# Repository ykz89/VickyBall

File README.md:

# VickyBall

Based on [KeyBall](https://github.com/Yowkees/keyball) and [roBa](https://github.com/kumamuk-git/roBa).

This project is forked from [roBa](https://github.com/kumamuk-git/roBa) with the main goal to convert the trackball sensor to use [VIK](https://github.com/sadekbaroudi/vik). The name VickyBall is a combination of [VIK](https://github.com/sadekbaroudi/vik) and [KeyBall](https://github.com/Yowkees/keyball).

Full list of changes:
- Sacrifice keys to make space for changes
- Add VIK connectors to trackball module and keyboard
- Change switch footprint to support MX, Choc and GLP switches
- Change microcontroller footprint from Xiao nrf52840 to Xiao nrf52840 Plus

## Build Guide

Todo

## Firmware

Todo

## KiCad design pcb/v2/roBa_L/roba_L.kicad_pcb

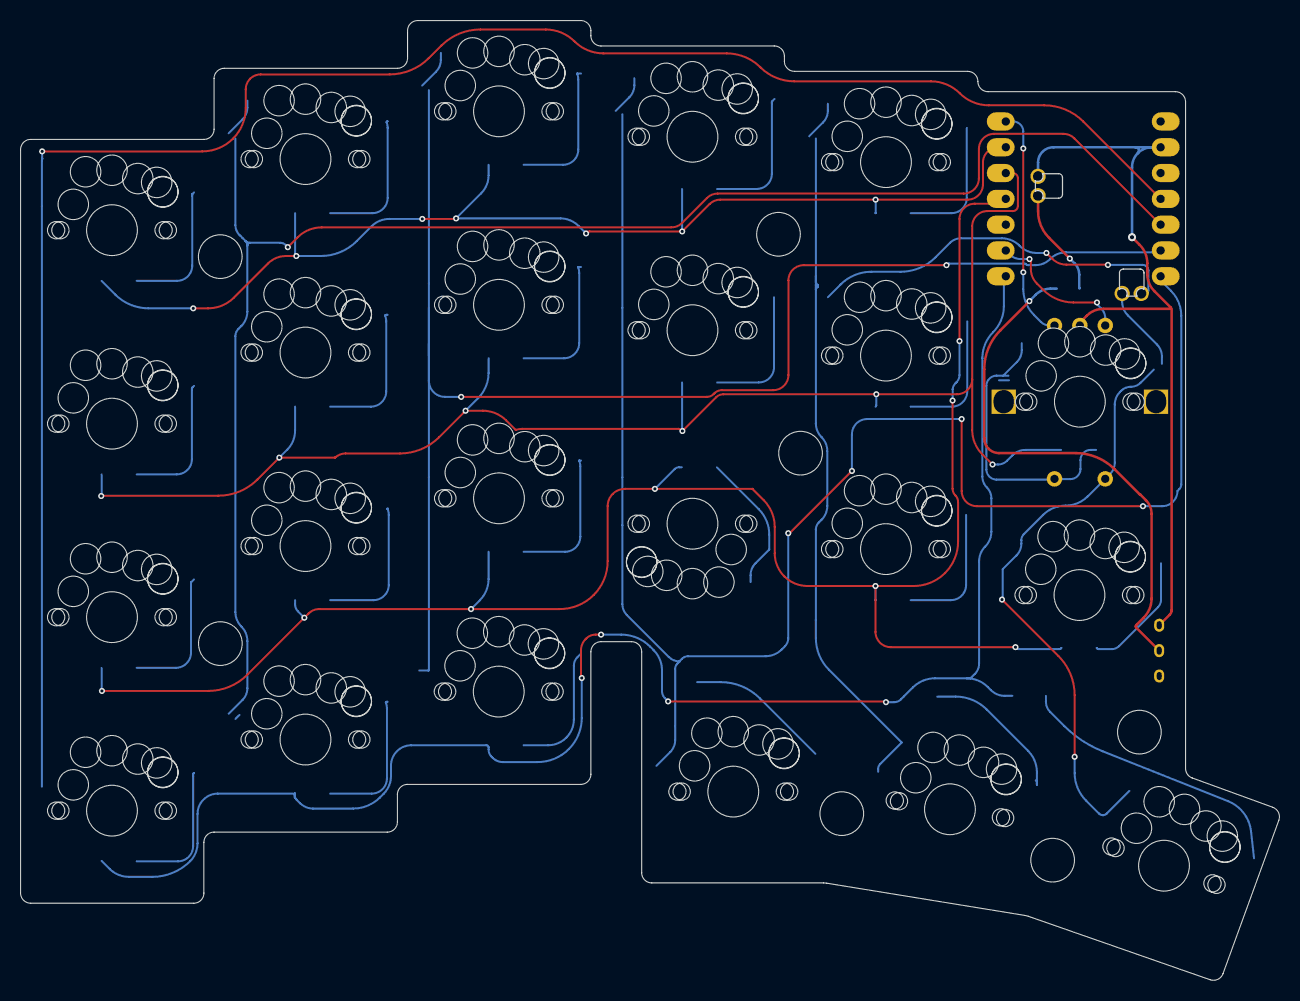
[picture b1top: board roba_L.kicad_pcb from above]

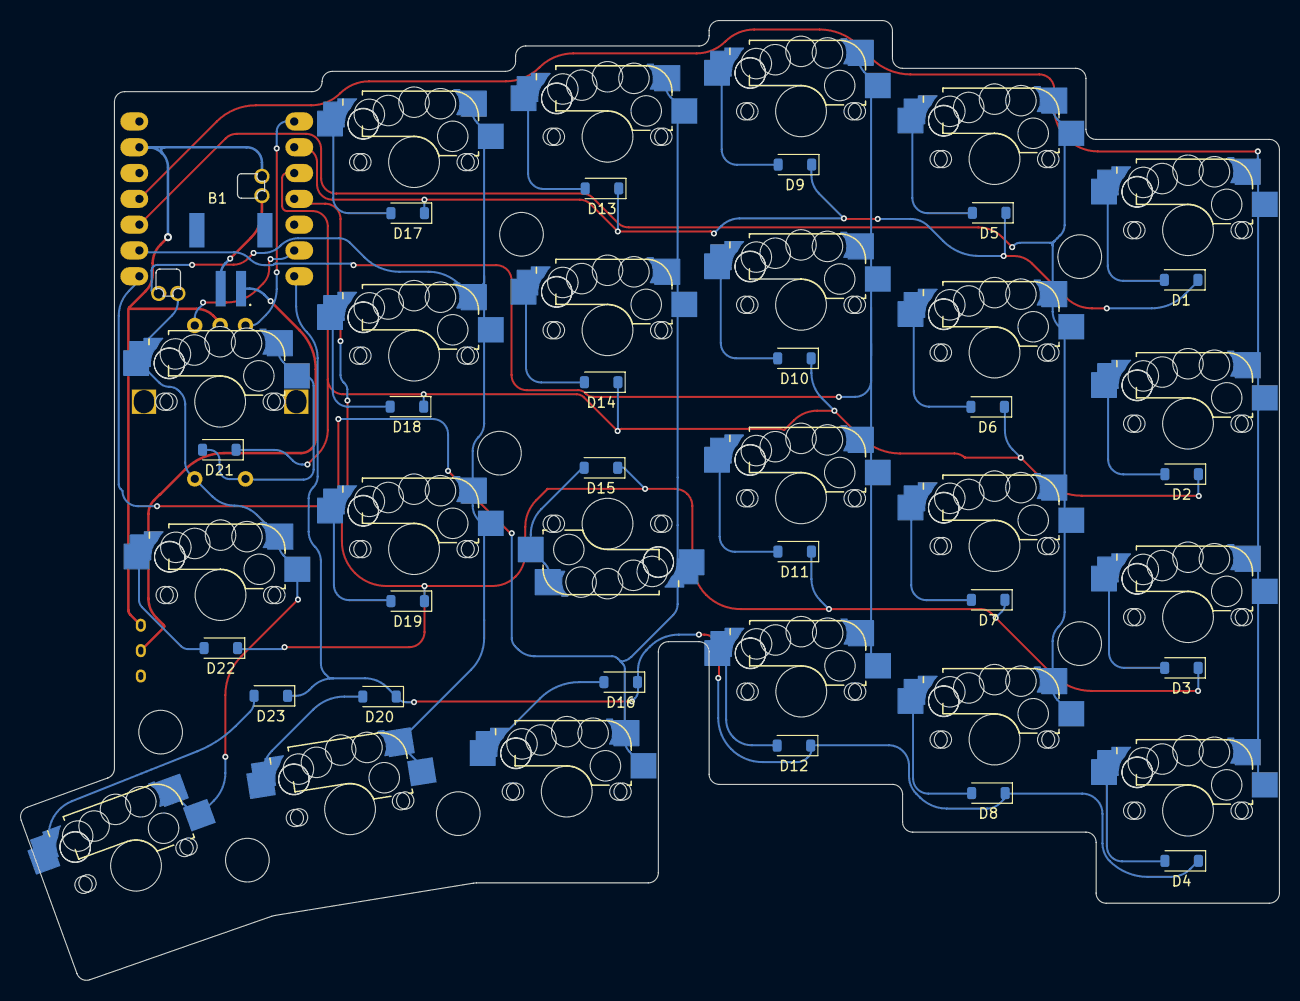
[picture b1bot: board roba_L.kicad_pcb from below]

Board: 2 copper layers, 123.9 x 94.5 mm, 56 parts (25 on the bottom side), 38 nets.

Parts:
B1: BATT; JST_S2B-PH-SM4-TB
D1, D2, D3, D4, D5, D6, D7, D8, D9, D10, D11, D12, D13, D14, D15, D16, D17, D18, D19, D20, D21, D22, D23: D; D_SOD-123
J1, J2, J3, J4, J5, J6, J7: Conn_01x01-Connector_Generic; MountingHole_4.3mm_M4
SW1, SW2, SW3, SW4, SW5, SW6, SW7, SW8, SW9, SW10, SW11, SW12, SW13, SW14, SW15, SW16, SW17, SW18, SW19, SW20, SW22, SW23: SW_PUSH; gateron-ks27-choc-v1-mx-hotswap-curved-pads
SW21: RotaryEncoder_Switch; gateron-ks27-choc-v1-mx-hotswap-ec12
SW24: SW_SPDT; TGSW_MSK-12D19
U1: XIAO_nRF52840_wBAT_wNFC_1

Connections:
Bat: B1.1 (+), U1.20 (BATT+)
Col0: SW1.2, SW2.2, SW3.2, SW4.2, U1.11 (P1.15_D10_MOSI)
Col1: SW5.2, SW6.2, SW7.2, SW8.2, U1.10 (P1.14_D9_MISO)
Col2: SW9.2, SW10.2, SW11.2, SW12.2, U1.9 (P1.13_D8_SCK)
Col3: SW13.2, SW14.2, SW15.1, SW16.2, U1.8 (P1.12_D7_RX)
Col4: SW17.2, SW18.2, SW19.2, SW20.2, U1.16 (NFC2_0.10)
Col5: SW21.1, SW21.2, SW22.2, SW23.2, U1.15 (NFC1_0.09)
GND: SW21.C, SW24.3 (C), U1.13 (GND), U1.21 (BATT-)
unnamed: B1.2 (-), SW24.2 (B)
unnamed: D1.2 (A), SW1.1
unnamed: D2.2 (A), SW2.1
unnamed: D3.2 (A), SW3.1
unnamed: D4.2 (A), SW4.1
unnamed: D5.2 (A), SW5.1
unnamed: D6.2 (A), SW6.1
unnamed: D7.2 (A), SW7.1
unnamed: D8.2 (A), SW8.1
unnamed: D9.2 (A), SW9.1
unnamed: D10.2 (A), SW10.1
unnamed: D11.2 (A), SW11.1
unnamed: D12.2 (A), SW12.1
unnamed: D13.2 (A), SW13.1
unnamed: D14.2 (A), SW14.1
unnamed: D15.2 (A), SW15.2
unnamed: D16.2 (A), SW16.1
unnamed: D17.2 (A), SW17.1
unnamed: D18.2 (A), SW18.1
unnamed: D19.2 (A), SW19.1
unnamed: D20.2 (A), SW20.1
unnamed: D21.2 (A), SW21.1, SW21.2
unnamed: D22.2 (A), SW22.1
unnamed: D23.2 (A), SW23.1
RE_A1: SW21.A, U1.6 (P0.05_A5_D5_SCL)
RE_B: SW21.B, U1.1 (P0.02_A0_D0)
Row0: D1.1 (K), D5.1 (K), D9.1 (K), D13.1 (K), D17.1 (K), U1.2 (P0.03_A1_D1)
Row1: D2.1 (K), D6.1 (K), D10.1 (K), D14.1 (K), D18.1 (K), D21.1 (K), U1.3 (P0.28_A2_D2)
Row2: D3.1 (K), D7.1 (K), D11.1 (K), D15.1 (K), D19.1 (K), D22.1 (K), U1.4 (P0.29_A3_D3)
Row3: D4.1 (K), D8.1 (K), D12.1 (K), D16.1 (K), D20.1 (K), D23.1 (K), U1.7 (P1.11_D6_TX)

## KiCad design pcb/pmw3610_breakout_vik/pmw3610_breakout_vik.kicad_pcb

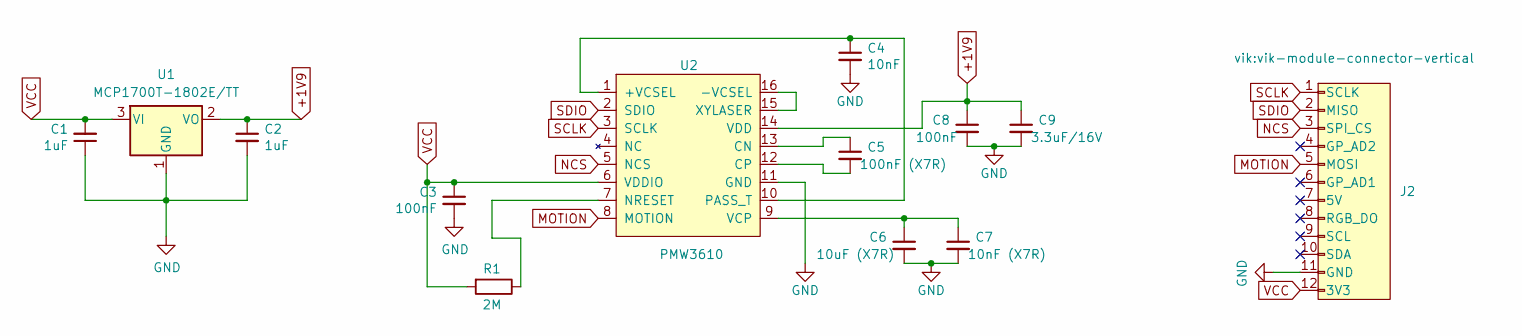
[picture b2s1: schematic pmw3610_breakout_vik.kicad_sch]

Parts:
C1, C2: 1uF; C_0603_1608Metric
C3, C8: 100nF; C_0603_1608Metric
C4: 10nF; C_0603_1608Metric
C5: 100nF (X7R); C_0603_1608Metric
C6: 10uF (X7R); C_0603_1608Metric
C7: 10nF (X7R); C_0603_1608Metric
C9: 3.3uF/16V; C_0603_1608Metric
J2: vik-module-connector; vik-module-connector-vertical
R1: 2M; R_0603_1608Metric
U1: MCP1700T-1802E/TT; SOT-23
U2: PMW3610; PMW3610DM-SUDU 16Pin

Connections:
+1V9: C2.1, C8.1, C9.1, U1.2 (VO), U2.14 (VDD)
GND: C1.1, C2.2, C3.2, C4.2, C6.2, C7.2, C8.2, C9.2, J2.11 (GND), U1.1 (GND), U2.11 (GND)
MOTION: J2.5 (MOSI), U2.8 (MOTION)
NCS: J2.3 (SPI_CS), U2.5 (NCS)
unnamed: C4.1, U2.1 (+VCSEL), U2.10 (PASS_T)
unnamed: U2.15 (XYLASER), U2.16 (-VCSEL)
unnamed: C5.1, U2.13 (CN)
unnamed: C5.2, U2.12 (CP)
unnamed: R1.1, U2.7 (NRESET)
unnamed: C6.1, C7.1, U2.9 (VCP)
SCLK: J2.1 (SCLK), U2.3 (SCLK)
SDIO: J2.2 (MISO), U2.2 (SDIO)
VCC: C1.2, C3.1, J2.12 (3V3), R1.2, U1.3 (VI), U2.6 (VDDIO)

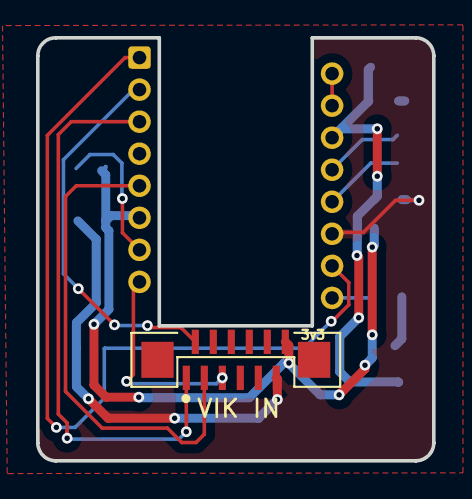
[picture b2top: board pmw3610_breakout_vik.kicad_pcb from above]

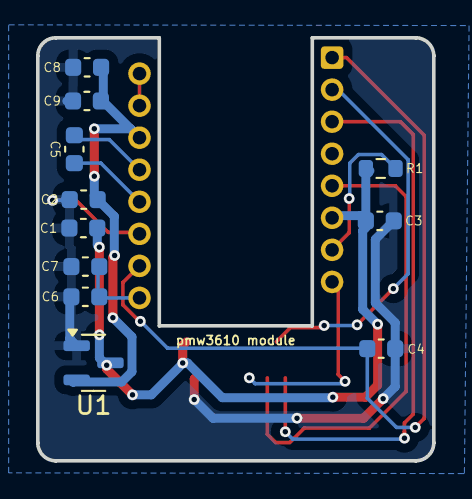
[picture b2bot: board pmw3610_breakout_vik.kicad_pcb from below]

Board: 2 copper layers, 22.0 x 23.5 mm, 13 parts (11 on the bottom side), 13 nets.

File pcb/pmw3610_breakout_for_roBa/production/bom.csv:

Designator,Footprint,Quantity,Value,LCSC Part #
"C1, C2",0603,2,1uF,C15849
"C3, C8",0603,2,100nF,C14663
C4,0603,1,10nF,C57112
C5,0603,1,100nF (X7R),C14663
C6,0603,1,10uF (X7R),C2959727
C7,0603,1,10nF (X7R),C57112
C9,0603,1,3.3uF/16V,C51412
J2,vik-module-connector-vertical,1,vik-module-connector,
R1,0603,1,2M,C22976
U1,SOT-23,1,MCP1700T-1802E/TT,
U2,PMW3610DM-SUDU 16Pin,1,PMW3610,

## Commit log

2024-11-07 Add VIK connector to trackball PCB, Remove earlier revisions
2024-11-09 Update pmw3610 breakout
2024-11-09 Change C1 value according to datasheet
2024-11-09 Fix capacitor values and generate production files
2024-11-13 Add production files, remove unused files
2024-11-13 Rename project and folders
2025-01-18 Add gitignore
2025-01-22 Update left PCB
2025-01-23 Update schematics and PCBs
2025-01-23 Minor changes
2025-02-15 Redo pmw3610 sensor board
